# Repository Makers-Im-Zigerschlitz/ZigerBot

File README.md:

# ZigerBot

Arduino shield to teach STEM / basic robotics

Current state: _planning_ 

## Goal

Create an Arduino(R) shield to help teach STEM / basic robotics

## General idea

We love teaching about mechanics, electricity, electronics and robotics. ZigerBot allows us to have a robust platform to teach the very basic of all this. Participants build their own robotic platform, solder the ZigerBot shield and connect both. ZigerBot can then be programmed via Arduino IDE or ArduBlockly .

## Inspiration
https://github.com/FuzzyNoodle/Fuzzy-Naked-Mega

## Features for first iteration
- Arduino compatible with Atmega2560 and CP2102
- Power-Input: Drives ZigerBot and powers Arduino
- Drives two DC motors, connect with screw terminals (DRV8833PW)
- Prepared for 1-2 Ultrasonic Range Sensor (SR04)
- Has an RGB LED matrix (5x5 or bigger, WS2812B)
- Can play simple melodies or signal tones
- Has 4 tactile button inputs
- Has 1-2 potentiometers
- Has 4 Servo Outputs

## Dependencies
- FastLED Library
- Arduino Bootloader

## Pin Configuration

We try to minimalize conflicts with different in- and output components and their libraries. 

# ZigerBot

Arduino shield to teach STEM / basic robotics

Current state: _planning_ 

## Goal

Create an Arduino(R) shield to help teach STEM / basic robotics

## General idea

We love teaching about mechanics, electricity, electronics and robotics. ZigerBot allows us to have a robust platform to teach the very basic of all this. Participants build their own robotic platform, solder the ZigerBot shield and connect both. ZigerBot can then be programmed via Arduino IDE or ArduBlockly .

## Inspiration
https://github.com/FuzzyNoodle/Fuzzy-Naked-Mega

## Features for first iteration
- Arduino compatible with Atmega2560 and CP2102
- Power-Input: Drives ZigerBot and powers Arduino
- Drives two DC motors, connect with screw terminals
- Prepared for 1 Ultrasonic Range Sensor (SR04)
- Has an RGB LED matrix (5x5 or bigger, WS2812B)
- Can play simple melodies or signal tones
- Has 4 tactile button inputs
- Has 1-2 potentiometers
- Has 4 Servo Outputs

## Dependencies
- FastLED Library
- Arduino IDE, bootloader and generally Arduino libraries

## Pin Configuration

We try to minimalize conflicts with different in- and output components and their libraries. 

~ PWM

- Timer 0 is used by delay(), millis() and micros() - these functions are useful to beginners
- Timer 2 is used by the tone library
- Timer 5 is used by the servo/megaservo library for up to 12 servos

| Arduino IDE pin | ZigerBot | Special function |
| --- | --- | --- |
| D0 | not assigned | Tx0 |
| D1 | not assigned | Rx0 |
| D2~ | not assigned | Timer 3 |
| D3~ | not assigned | Timer 3 |
| D4~ | not assigned | Timer 0 |
| D5~ | **Motor A Input 1** | Timer 3 |
| D6~ | **Motor A Input 2** | Timer 4 |
| D7~ | **Motor B Input 1** | Timer 4 |
| D8~ | **Motor B Input 2** | Timer 4 |
| D9~ | not assigned | Timer 2 |
| D10~ | not assigned | Timer 2 |
| D11~ | not assigned | Timer 1 |
| D12~ | not assigned | Timer 1 |
| D13~ | not assigned | Timer 0, built-in LED|
| D14 | not assigned | Tx3 |
| D15 | not assigned | Rx3 |
| D16 | not assigned | Tx2 |
| D17 | not assigned | Rx2 |
| D18 | not assigned | Tx1 |
| D19 | not assigned | Rx1 |
| D20 | not assigned | SDA |
| D21 | not assigned | SCL |
| D22 | **Ultrasonic sensor SR04 trigger pin** | none |
| D23 | **Ultrasonic sensor SR04 echo pin** | none |
| D24 | **LED-Matrix data out** | none |
| D25 | **Piezo speaker** | none |
| D26 | **Tactile button 1** | none |
| D27 | **Tactile button 2** | none |
| D28 | **Tactile button 3** | none |
| D29 | **Tactile button 4** | none |
| D30 | **Servo 1** | none |
| D31 | **Servo 2** | none |
| D32 | **Servo 3** | none |
| D33 | **Servo 4** | none |
| D34 | not assigned | none |
| D35 | not assigned | none |
| D36 | not assigned | none |
| D37 | not assigned | none |
| D38 | not assigned | none |
| D39 | not assigned | none |
| D40 | not assigned | none |
| D41 | not assigned | none |
| D42 | not assigned | none |
| D43 | not assigned | none |
| D44~ | not assigned | Timer 5 |
| D45~ | not assigned | Timer 5 |
| D46~ | not assigned | Timer 5 |
| D47 | not assigned | none |
| D48 | not assigned | none |
| D49 | not assigned | none |
| D50 | not assigned | MISO |
| D51 | not assigned | MOSI |
| D52 | not assigned | SCK |
| D53 | not assigned | SS |
| --- | --- | --- |
| A0 | **Potentiometer 1** | none |
| A1 | **Potentiometer 2** | none |
| A2 | not assigned | none |
| A3 | not assigned | none |
| A4 | not assigned | none |
| A5 | not assigned | none |
| A6 | not assigned | none |
| A7 | not assigned | none |
| A8 | not assigned | none |
| A9 | not assigned | none |
| A10 | not assigned | none |
| A11 | not assigned | none |
| A12 | not assigned | none |
| A13 | not assigned | none |
| A14 | not assigned | none |
| A15 | not assigned | none |

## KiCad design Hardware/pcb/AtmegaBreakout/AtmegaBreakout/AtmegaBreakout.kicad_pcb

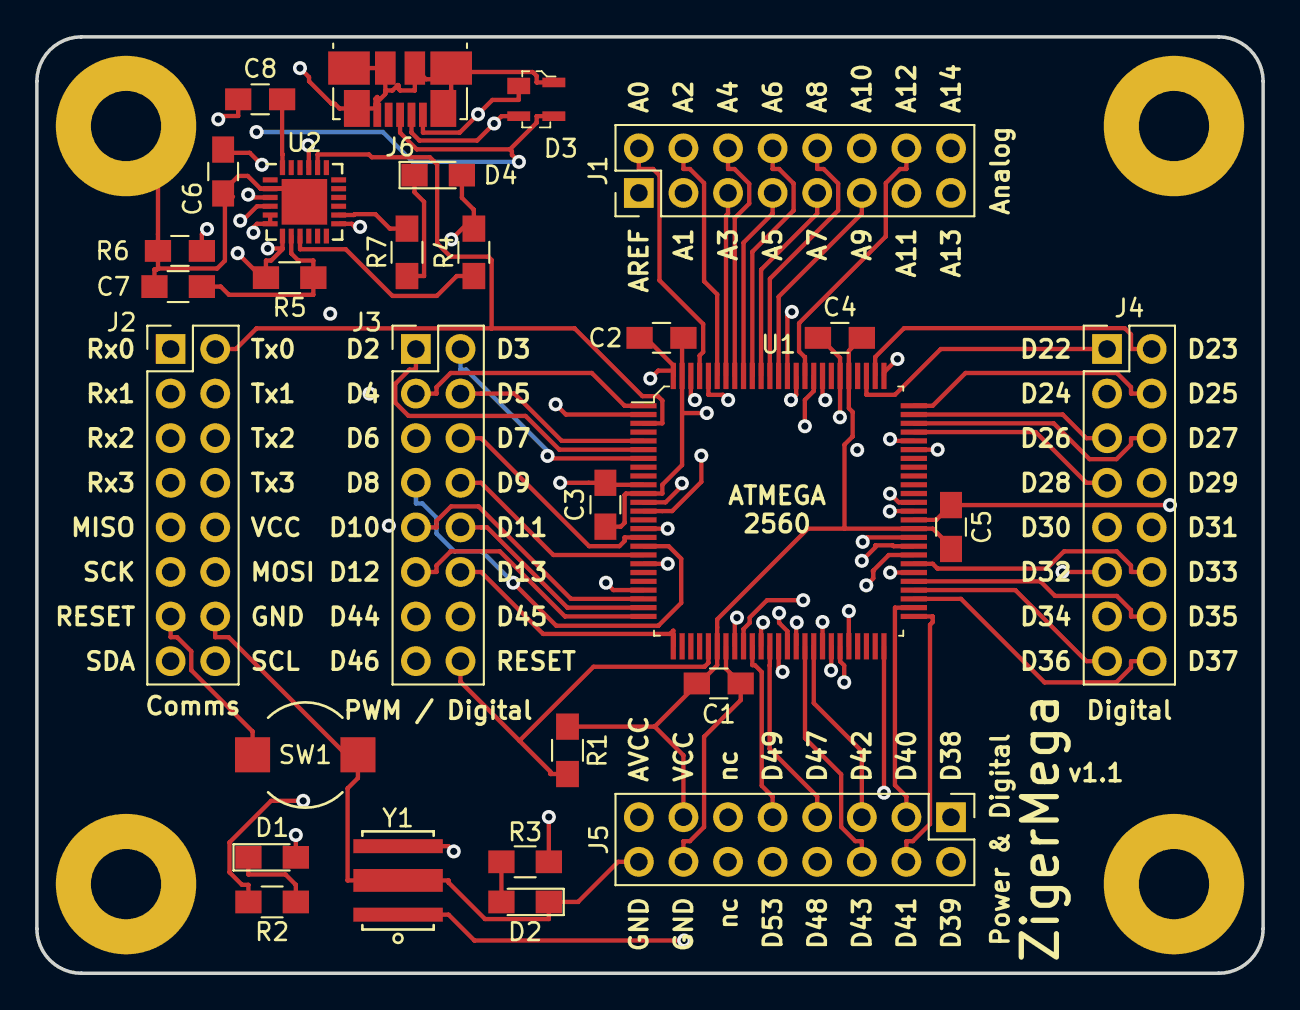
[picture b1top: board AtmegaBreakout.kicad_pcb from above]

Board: 4 copper layers, 69.9 x 53.3 mm, 33 parts (0 on the bottom side), 85 nets.

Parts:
C1, C2, C3, C4, C5, C6, C8: 0.1uF; C_0805_HandSoldering
C7: 4.7uF; C_0805_HandSoldering
D1: LED USB Rx; LED_0805_HandSoldering
D2: LED L; LED_0805_HandSoldering
D3: SP0503BAHTG; SOT-143-4
D4: LED USB Tx; LED_0805_HandSoldering
J1: ANALOG; Pin_Header_Straight_2x08_Pitch2.54mm
J2: POWER and COMMS; Pin_Header_Straight_2x08_Pitch2.54mm
J3: DIGITAL1; Pin_Header_Straight_2x08_Pitch2.54mm
J4: DIGITAL2; Pin_Header_Straight_2x08_Pitch2.54mm
J5: DIGITAL3; Pin_Header_Straight_2x08_Pitch2.54mm
J6: USB_B_Micro; USB_Micro-B_Molex_47346-0001
MH1, MH2, MH3, MH4: MountingHole_Pad; MountingHole_4mm_Pad
R1: 47k; R_0805_HandSoldering
R2, R3, R4, R7: 1k; R_0805_HandSoldering
R5: 22.1k; R_0805_HandSoldering
R6: 47.5k; R_0805_HandSoldering
SW1: EVP-ASAC1A
U1: ATMEGA2560-16AU; TQFP-100_14x14mm
U2: CP2102N-A01-GQFN24; QFN-24-1EP_4x4mm_Pitch0.5mm
Y1: 16MHz Ceramic Resonator; AWSCR-MT

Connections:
/A0: J1.2, U1.97
/A1: J1.3, U1.96
/A2: J1.4, U1.95
/A3: J1.5, U1.94
/A4: J1.6, U1.93
/A5: J1.7, U1.92
/A6: J1.8, U1.91
/A7: J1.9, U1.90
/A8: J1.10, U1.89
/A9: J1.11, U1.88
/A10: J1.12, U1.87
/A11: J1.13, U1.86
/A12: J1.14, U1.85
/A13: J1.15, U1.84
/A14: J1.16, U1.83
/AREF: J1.1, U1.98
/AVCC: C2.2, J5.15, U1.100
/D2: J3.1, U1.6
/D3: J3.2, U1.7
/D4: J3.3, U1.1
/D5: J3.4, U1.5
/D6: J3.5, U1.15
/D7: J3.6, U1.16
/D8: J3.7, U1.17
/D9: J3.8, U1.18
/D10: J3.9, U1.23
/D11: J3.10, U1.24
/D12: J3.11, U1.25
/D13: J3.12, R3.2, U1.26
/D22: J4.1, U1.78
/D23: J4.2, U1.77
/D24: J4.3, U1.76
/D25: J4.4, U1.75
/D26: J4.5, U1.74
/D27: J4.6, U1.73
/D28: J4.7, U1.72
/D29: J4.8, U1.71
/D30: J4.9, U1.60
/D31: J4.10, U1.59
/D32: J4.11, U1.58
/D33: J4.12, U1.57
/D34: J4.13, U1.56
/D35: J4.14, U1.55
/D36: J4.15, U1.54
/D37: J4.16, U1.53
/D38: J5.1, U1.50
/D39: J5.2, U1.70
/D40: J5.3, U1.52
/D41: J5.4, U1.51
/D42: J5.5, U1.42
/D43: J5.6, U1.41
/D44: J3.13, U1.40
/D45: J3.14, U1.39
/D46: J3.15, U1.38
/D47: J5.7, U1.37
/D48: J5.8, U1.36
/D49: J5.9, U1.35
/D53-SS: J5.10, U1.19
/DTR: C8.2, U2.24
/MISO-D50: J2.9, U1.22
/RESET: C8.1, J2.13, J3.16, R1.2, SW1.1, U1.30
/Rx0-D0: J2.1, U1.2, U2.21
/Rx1-D19: J2.3, U1.45
/Rx2-D17: J2.5, U1.12
/Rx3-D15: J2.7, U1.63
/SCL-D21: J2.16, U1.43
/SDA-D20: J2.15, U1.44
/Tx0-D1: J2.2, U1.3, U2.20
/Tx1-D18: J2.4, U1.46
/Tx2-D16: J2.6, U1.13
/Tx3-D14: J2.8, U1.64
/VIO: C6.2, C7.1, D1.2, D4.2, R4.2, U2.5, U2.6
/XTAL1: U1.34, Y1.3
/XTAL2: U1.33, Y1.1
GND: C1.1, C2.1, C3.1, C4.1, C5.1, C6.1, C7.2, D2.1, D3.1, J2.14, J5.14, J5.16, J6.5, J6.6, MH1.1, MH2.1, MH3.1, MH4.1, R6.1, SW1.2, U1.11, U1.32, U1.62, U1.81, U1.99, U2.2, U2.25, Y1.2
unnamed: D1.1, R2.1
unnamed: D2.2, R3.1
unnamed: D3.3, J6.2, U2.4
unnamed: D3.4, J6.3, U2.3
unnamed: D4.1, R7.1
unnamed: R2.2, U2.13
unnamed: R4.1, U2.9
unnamed: R5.1, R6.2, U2.8
unnamed: R7.2, U2.14
VCC: C1.2, C3.2, C4.2, C5.2, D3.2, J2.10, J5.13, J6.1, R1.1, R5.2, U1.10, U1.31, U1.61, U1.80, U2.7

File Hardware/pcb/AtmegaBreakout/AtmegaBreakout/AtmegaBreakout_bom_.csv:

Component,Description,Part,References,Value,Footprint,Quantity Per PCB,Datasheet,MPN,Digi-Key_PN,Category,Status,Family,DK_Datasheet_Link,DK_Detail_Page,Manufacturer
1,Unpolarized capacitor,C_Small,C1 C2 C3 C4 C5 C6 C8,0.1uF,C_0805_HandSoldering,7,~,CC0805ZRY5V9BB104,311-1361-1-ND,,,,,,
2,Unpolarized capacitor,C_Small,C7,4.7uF,C_0805_HandSoldering,1,~,CC0805ZRY5V6BB475,311-1371-1-ND,,,,,,
3,"LED, small symbol",LED_Small,D2,LED L,LED_0805_HandSoldering,1,~,LTST-C170GKT,160-1179-1-ND,,,,,,
4,"LED, small symbol",LED_Small,D1,LED USB Rx,LED_0805_HandSoldering,1,~,LTST-C171KSKT,160-1428-1-ND,,,,,,
5,"LED, small symbol",LED_Small,D4,LED USB Tx,LED_0805_HandSoldering,1,~,LTST-C171KSKT,160-1428-1-ND,,,,,,
6,TVS DIODE 5.5V 8.5V SOT143-4,SP0503BAHTG,D3,SP0503BAHTG,SOT-143-4,1,http://www.littelfuse.com/~/media/files/littelfuse/technical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,SP0503BAHTG,F2715CT-ND,Circuit Protection,Active,TVS - Diodes,http://www.littelfuse.com/~/media/files/littelfuse/technical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,/product-detail/en/littelfuse-inc/SP0503BAHTG/F2715CT-ND/1154322,Littelfuse Inc.
7,"Generic connector, double row, 02x08, odd/even pin numbering scheme (row 1 odd numbers, row 2 even numbers), script generated (kicad-library-utils/schlib/autogen/connector/)",Conn_02x08_Odd_Even,J1,ANALOG,Pin_Header_Straight_2x08_Pitch2.54mm,1,~,68602-116HLF,609-3364-ND,,,,,,
8,"Generic connector, double row, 02x08, odd/even pin numbering scheme (row 1 odd numbers, row 2 even numbers), script generated (kicad-library-utils/schlib/autogen/connector/)",Conn_02x08_Odd_Even,J3,DIGITAL1,Pin_Header_Straight_2x08_Pitch2.54mm,1,~,68602-116HLF,609-3364-ND,,,,,,
9,"Generic connector, double row, 02x08, odd/even pin numbering scheme (row 1 odd numbers, row 2 even numbers), script generated (kicad-library-utils/schlib/autogen/connector/)",Conn_02x08_Odd_Even,J4,DIGITAL2,Pin_Header_Straight_2x08_Pitch2.54mm,1,~,68602-116HLF,609-3364-ND,,,,,,
10,"Generic connector, double row, 02x08, odd/even pin numbering scheme (row 1 odd numbers, row 2 even numbers), script generated (kicad-library-utils/schlib/autogen/connector/)",Conn_02x08_Odd_Even,J5,DIGITAL3,Pin_Header_Straight_2x08_Pitch2.54mm,1,~,68602-116HLF,609-3364-ND,,,,,,
11,"Generic connector, double row, 02x08, odd/even pin numbering scheme (row 1 odd numbers, row 2 even numbers), script generated (kicad-library-utils/schlib/autogen/connector/)",Conn_02x08_Odd_Even,J2,POWER and COMMS,Pin_Header_Straight_2x08_Pitch2.54mm,1,~,68602-116HLF,609-3364-ND,,,,,,
12,USB Micro Type B connector,USB_B_Micro,J6,USB_B_Micro,USB_Micro-B_Molex_47346-0001,1,~,47346-0001,WM17141CT-ND,,,,,,
13,Resistor,R,R2 R3 R4 R7,1k,R_0805_HandSoldering,4,~,RC0805FR-071KL,311-1.00KCRCT-ND,,,,,,
14,Resistor,R,R5,22.1k,R_0805_HandSoldering,1,~,RC0805FR-0722K1L,311-22.1KCRCT-ND,,,,,,
15,Resistor,R,R6,47.5k,R_0805_HandSoldering,1,~,RC0805FR-0747K5L,311-47.5KCRCT-ND,,,,,,
16,Resistor,R,R1,47k,R_0805_HandSoldering,1,~,RC0805FR-0747KL,311-47.0KCRCT-ND,,,,,,
17,"Push button switch, generic, two pins",SW_Push,SW1,EVP-ASAC1A,EVP-ASAC1A,1,,EVP-ASAC1A,P16854CT-ND,,,,,,
18,IC MCU 8BIT 256KB FLASH 100TQFP,ATMEGA2560-16AU,U1,ATMEGA2560-16AU,TQFP-100_14x14mm,1,http://ww1.microchip.com/downloads/en/DeviceDoc/Atmel-2549-8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,ATMEGA2560-16AU,ATMEGA2560-16AU-ND,Integrated Circuits (ICs),Active,Embedded - Microcontrollers,http://ww1.microchip.com/downloads/en/DeviceDoc/Atmel-2549-8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,/product-detail/en/microchip-technology/ATMEGA2560-16AU/ATMEGA2560-16AU-ND/735455,Microchip Technology
19,USB to UART master bridge,CP2102N-A01-GQFN24,U2,CP2102N-A01-GQFN24,QFN-24-1EP_4x4mm_Pitch0.5mm,1,http://www.silabs.com/support%20documents/technicaldocs/cp21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,CP2102N-A01-GQFN24,336-4737-1-ND,,,,,,
20,Three pin ceramic resonator,Resonator,Y1,16MHz Ceramic Resonator,AWSCR-MT,1,~,AWSCR-16.00MTD-T,535-9362-1-ND,,,,,,





Component Groups:,20
Component Count:,29
Fitted Components:,29
Number of PCBs:,1
Total components:,29
Schematic Version:,
Schematic Date:,
BoM Date:,27/01/2019 21:54:11
Schematic Source:,C:\Users\Mike\Documents\GitHub\ZigerBot\Hardware\pcb\AtmegaBreakout\AtmegaBreakout\AtmegaBreakout.sch
KiCad Version:,Eeschema (5.0.0)

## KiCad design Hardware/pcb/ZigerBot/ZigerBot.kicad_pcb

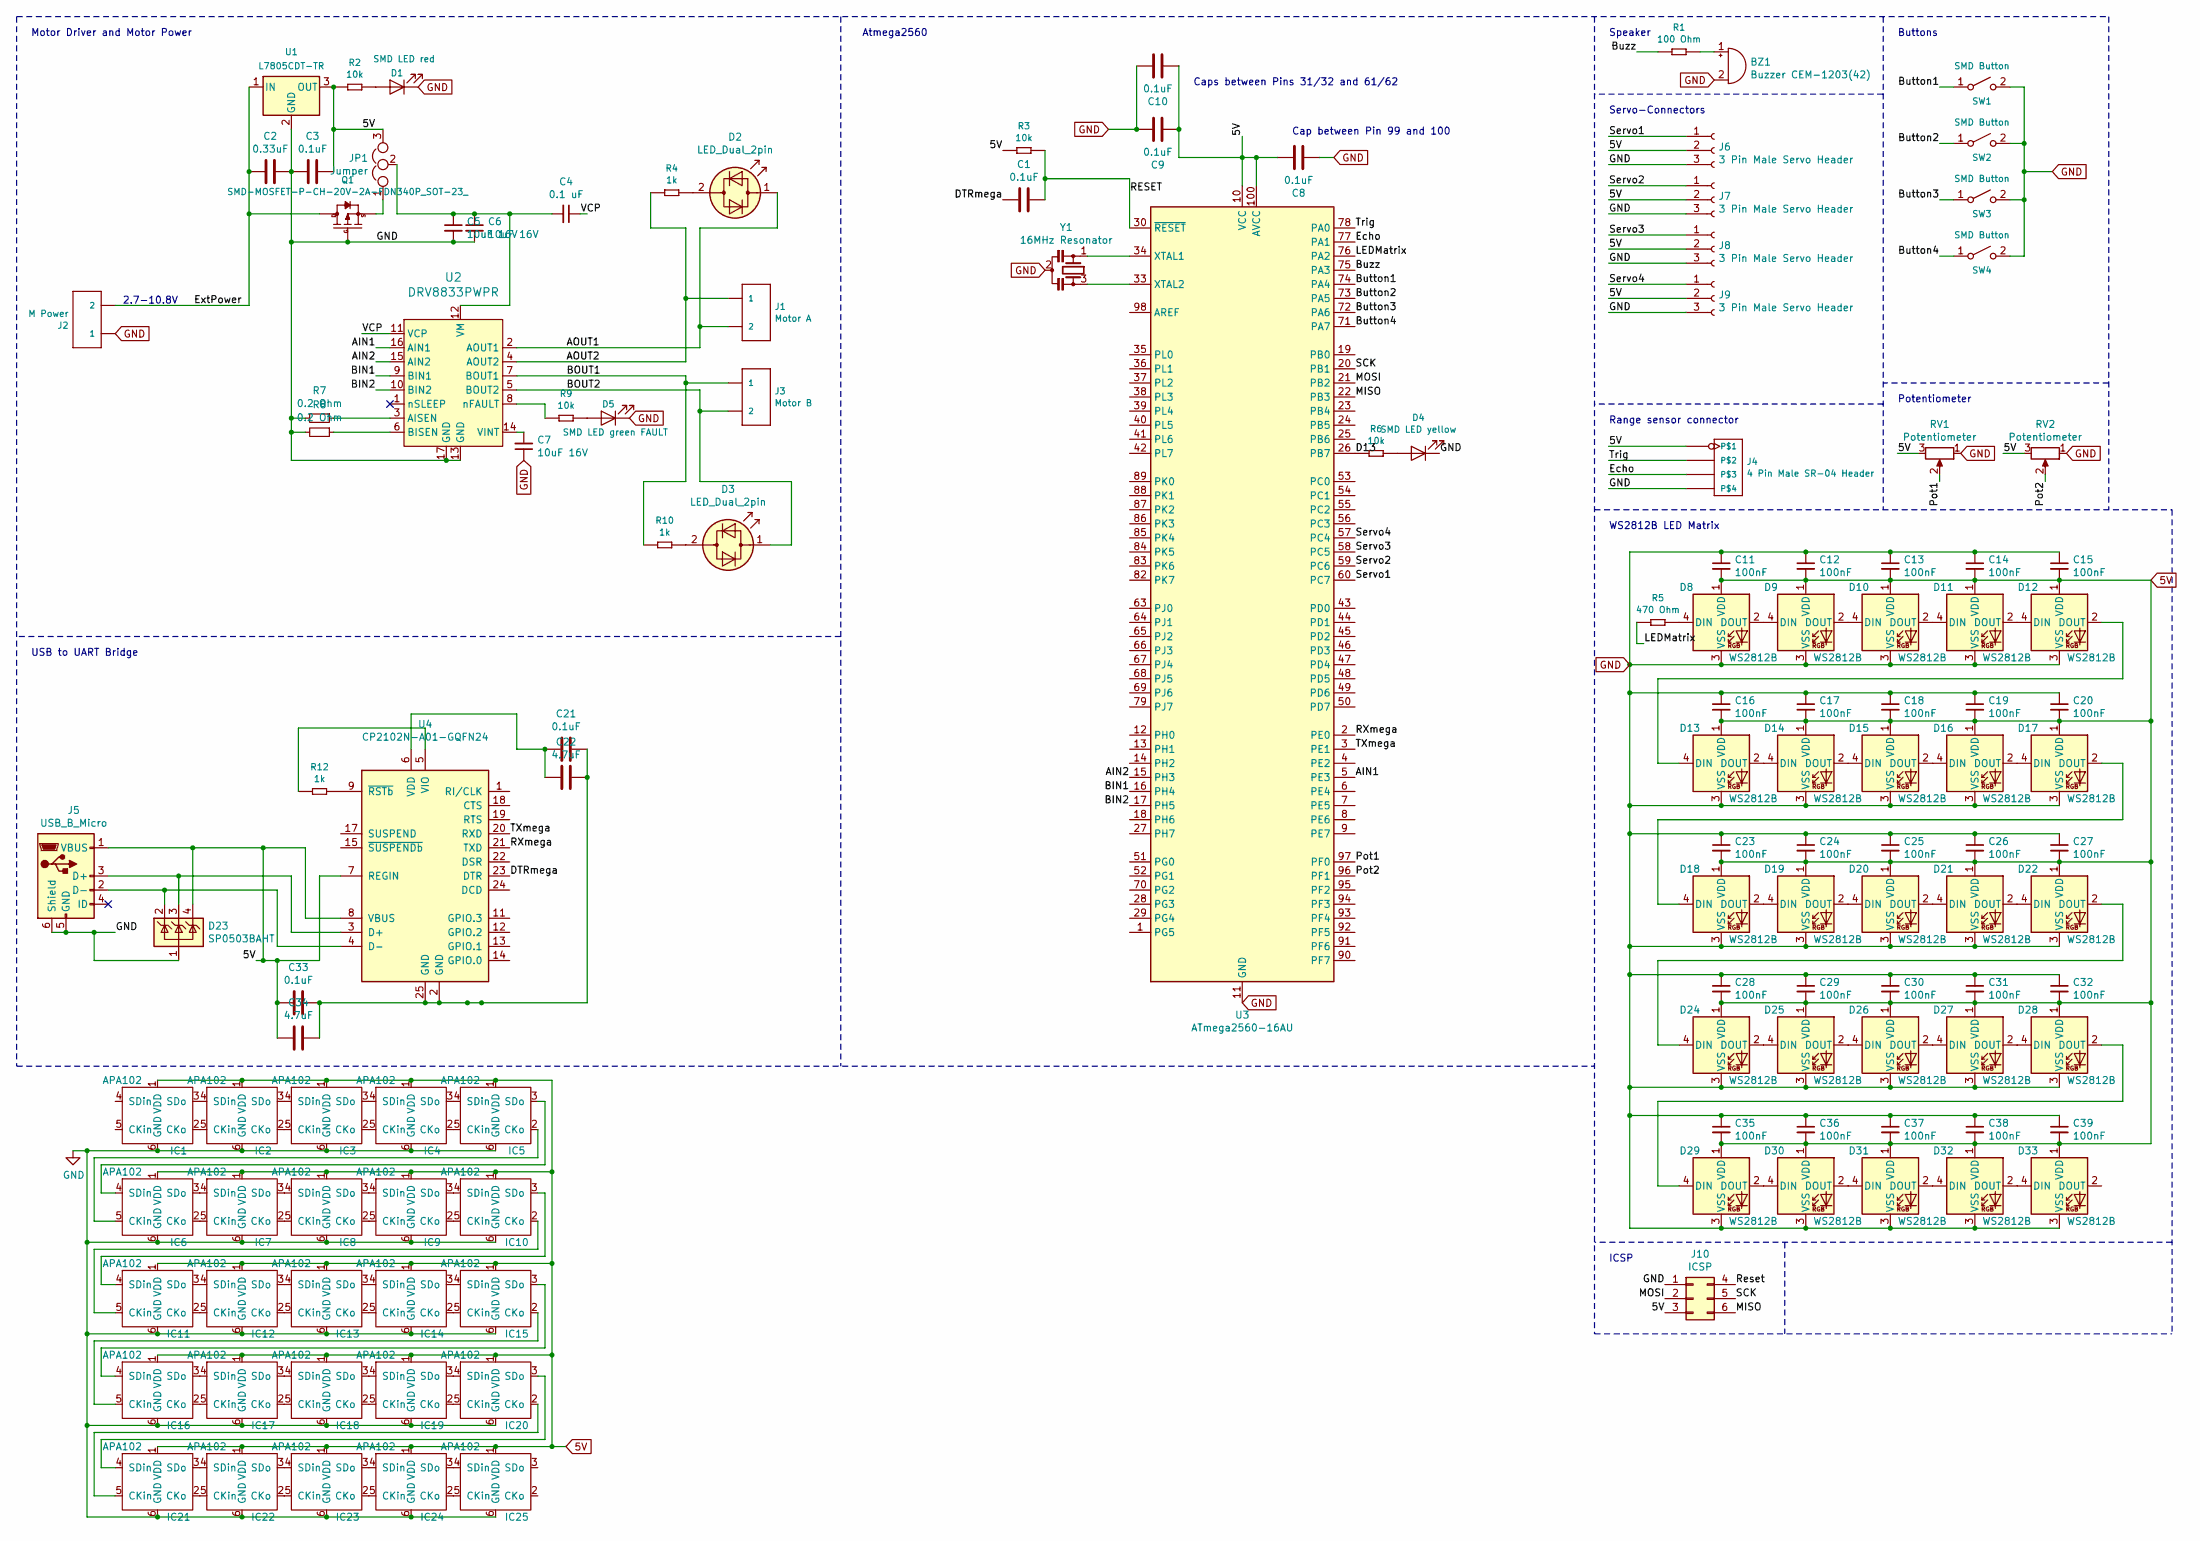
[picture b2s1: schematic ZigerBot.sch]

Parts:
BZ1: Buzzer CEM-1203(42); BUZZER_CEM-1203(24)_12mm_6.5mm_0.6mm; Digi-Key_PN 102-1153-ND
C1, C3, C8, C9, C10, C21, C33: 0.1uF; C_0805; Digi-Key_PN 311-1141-1-ND
C2: 0.33uF; C_0805; Digi-Key_PN 311-3385-1-ND
C4: 0.1 uF; C_0805; Digi-Key_PN 311-1141-1-ND
C5, C6, C7: 10uF 16V; C_0805; Digi-Key_PN 490-3886-1-ND
C11, C12, C13, C14, C15, C16, C17, C18, C19, C20, C23, C24, C25, C26, C27, C28, C29, C30, C31, C32, C35, C36, C37, C38, C39: 100nF; C_0805; Digi-Key_PN 311-1141-1-ND
C22, C34: 4.7uF; C_0805; Digi-Key_PN 311-1863-1-ND
D1: SMD LED red; LED_0603; Digi-Key_PN 160-1436-1-ND
D2, D3: LED_Dual_2pin; LED_D5.0mm; MPN LTL-293SJW; Digi-Key_PN 160-1038-ND
D4: SMD LED yellow; LED_0603; Digi-Key_PN 160-1437-1-ND
D5: SMD LED green FAULT; LED_0603; Digi-Key_PN 160-1435-1-ND
D8, D9, D10, D11, D12, D13, D14, D15, D16, D17, D18, D19, D20, D21, D22, D24, D25, D26, D27, D28, D29, D30, D31, D32, D33: WS2812B; LED_WS2812B-PLCC4; Digi-Key_PN 1528-1104-ND
D23: SP0503BAHT; SOT-143_Handsoldering; Digi-Key_PN F2715CT-ND
IC1, IC2, IC3, IC4, IC5, IC6, IC7, IC8, IC9, IC10, IC11, IC12, IC13, IC14, IC15, IC16, IC17, IC18, IC19, IC20, IC21, IC22, IC23, IC24, IC25: APA102; APA102-2020
J1: Motor A; H2-5.0-10.5X8.0MM; Digi-Key_PN ED2609-ND
J2: M Power; H2-5.0-10.5X8.0MM; Digi-Key_PN ED2609-ND
J3: Motor B; H2-5.0-10.5X8.0MM; Digi-Key_PN ED2609-ND
J4: 4 Pin Male SR-04 Header; H4-2.54; MPN P125-1104A0BS116A1; Digi-Key_PN 732-5317-ND
J5: USB_B_Micro; USB_Micro-B_Molex-105017-0001; Digi-Key_PN 609-4616-1-ND
J6, J7, J8, J9: 3 Pin Male Servo Header; Pin_Header_Straight_1x03_Pitch2.54mm; Digi-Key_PN 732-5316-ND
J10: ICSP; Digi-Key_PN 609-3218-ND
JP1: Jumper; Pin_Header_Straight_1x03_Pitch2.54mm; Digi-Key_PN 732-5316-ND
Q1: SMD-MOSFET-P-CH-20V-2A-FDN340P_SOT-23_; SOT-23; MPN FDN340P; Digi-Key_PN FDN340PCT-ND
R1: 100 Ohm; R_0805; Digi-Key_PN 311-100CRCT-ND
R2, R3, R6, R9: 10k; R_0805; Digi-Key_PN 311-10.0KCRCT-ND
R4, R10, R12: 1k; R_0805; Digi-Key_PN 311-1.00KCRCT-ND
R5: 470 Ohm; R_0805; Digi-Key_PN 311-470CRCT-ND
R7, R8: 0.2 Ohm; R_0805; Digi-Key_PN 311-.20SCT-ND
RV1, RV2: Potentiometer; Potentiometer_Trimmer-EVM3E; Digi-Key_PN 1528-1997-ND
SW1, SW2, SW3, SW4: SMD Button; SW_SPST_SKQG; MPN PTS645SK50SMTR92 LFS; Digi-Key_PN CKN9087CT-ND
U1: L7805CDT-TR; TO-252-2; MPN L7805CDT-TR; Digi-Key_PN 497-7255-1-ND
U2: DRV8833PWPR; TSSOP-16-1EP_W4.40mm; MPN DRV8833PWPR; Digi-Key_PN 296-29434-1-ND
U3: ATmega2560-16AU; TQFP-100_14x14mm_Pitch0.5mm; Digi-Key_PN ATMEGA2560-16AU-ND
U4: CP2102N-A01-GQFN24; QFN-24-1EP_4x4mm_Pitch0.5mm; Digi-Key_PN 336-4737-1-ND
Y1: 16MHz Resonator; Resonator_SMD_muRata_CSTNE16M0V530000_3pin_3.2x1.3x0.9mm; Digi-Key_PN CSTNE16M0V53C000R0

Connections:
5V: C3.1, C8.1, C9.2, C10.2, C11.2, C12.2, C13.2, C14.2, C15.2, C16.2, C17.2, C18.2, C19.2, C20.2, C23.2, C24.2, C25.2, C26.2, C27.2, C28.2, C29.2, C30.2, C31.2, C32.2, C33.2, C34.2, C35.2, C36.2, C37.2, C38.2, C39.2, D8.1 (VDD), D9.1 (VDD), D10.1 (VDD), D11.1 (VDD), D12.1 (VDD), D13.1 (VDD), D14.1 (VDD), D15.1 (VDD), D16.1 (VDD), D17.1 (VDD), D18.1 (VDD), D19.1 (VDD), D20.1 (VDD), D21.1 (VDD), D22.1 (VDD), D23.4 (K), D24.1 (VDD), D25.1 (VDD), D26.1 (VDD), D27.1 (VDD), D28.1 (VDD), D29.1 (VDD), D30.1 (VDD), D31.1 (VDD), D32.1 (VDD), D33.1 (VDD), IC1.1 (VDD), IC2.1 (VDD), IC3.1 (VDD), IC4.1 (VDD), IC5.1 (VDD), IC6.1 (VDD), IC7.1 (VDD), IC8.1 (VDD), IC9.1 (VDD), IC10.1 (VDD), IC11.1 (VDD), IC12.1 (VDD), IC13.1 (VDD), IC14.1 (VDD), IC15.1 (VDD), IC16.1 (VDD), IC17.1 (VDD), IC18.1 (VDD), IC19.1 (VDD), IC20.1 (VDD), IC21.1 (VDD), IC22.1 (VDD), IC23.1 (VDD), IC24.1 (VDD), IC25.1 (VDD), J4.1, J5.1 (VBUS), J6.2, J7.2, J8.2, J9.2, J10.3, JP1.3, R2.1, R3.1, RV1.3, RV2.3, U1.3 (OUT), U3.10 (VCC), U3.31 (VCC), U3.61 (VCC), U3.80 (VCC), U3.100 (AVCC), U4.7 (REGIN), U4.8 (VBUS)
/AIN1: U2.16 (AIN1), U3.5 (PE3)
/AIN2: U2.15 (AIN2), U3.15 (PH3)
/AOUT1: D2.1 (KA), J1.2, U2.2 (AOUT1)
/AOUT2: J1.1, R4.1, U2.4 (AOUT2)
/BIN1: U2.9 (BIN1), U3.16 (PH4)
/BIN2: U2.10 (BIN2), U3.17 (PH5)
/BOUT1: J3.1, R10.1, U2.7 (BOUT1)
/BOUT2: D3.1 (KA), J3.2, U2.5 (BOUT2)
/Button1: SW1.1 (A), U3.74 (PA4)
/Button2: SW2.1 (A), U3.73 (PA5)
/Button3: SW3.1 (A), U3.72 (PA6)
/Button4: SW4.1 (A), U3.71 (PA7)
/Buzz: R1.1, U3.75 (PA3)
/D13: R6.1, U3.26 (PB7)
/DTRmega: C1.2, U4.23 (DTR)
/Echo: J4.3, U3.77 (PA1)
/ExtPower: C2.2, J2.2, Q1.3 (D), U1.1 (IN)
/LEDMatrix: R5.1, U3.76 (PA2)
/MISO: J10.6, U3.22 (PB3)
/MOSI: J10.2, U3.21 (PB2)
/Pot1: RV1.2, U3.97 (PF0)
/Pot2: RV2.2, U3.96 (PF1)
/RESET: C1.1, R3.2, U3.30 (~RESET)
/RXmega: U3.2 (PE0), U4.21 (TXD)
/Reset: J10.4
/SCK: J10.5, U3.20 (PB1)
/Servo1: J6.1, U3.60 (PC7)
/Servo2: J7.1, U3.59 (PC6)
/Servo3: J8.1, U3.58 (PC5)
/Servo4: J9.1, U3.57 (PC4)
/TXmega: U3.3 (PE1), U4.20 (RXD)
/Trig: J4.2, U3.78 (PA0)
/VCP: C4.1, U2.11 (VCP)
GND: BZ1.2 (+), C2.1, C3.2, C5.2, C6.2, C7.1, C8.2, C9.1, C10.1, C11.1, C12.1, C13.1, C14.1, C15.1, C16.1, C17.1, C18.1, C19.1, C20.1, C23.1, C24.1, C25.1, C26.1, C27.1, C28.1, C29.1, C30.1, C31.1, C32.1, C35.1, C36.1, C37.1, C38.1, C39.1, D1.1 (K), D4.1 (K), D5.1 (K), D8.3 (VSS), D9.3 (VSS), D10.3 (VSS), D11.3 (VSS), D12.3 (VSS), D13.3 (VSS), D14.3 (VSS), D15.3 (VSS), D16.3 (VSS), D17.3 (VSS), D18.3 (VSS), D19.3 (VSS), D20.3 (VSS), D21.3 (VSS), D22.3 (VSS), D23.1 (A), D24.3 (VSS), D25.3 (VSS), D26.3 (VSS), D27.3 (VSS), D28.3 (VSS), D29.3 (VSS), D30.3 (VSS), D31.3 (VSS), D32.3 (VSS), D33.3 (VSS), IC1.6 (GND), IC2.6 (GND), IC3.6 (GND), IC4.6 (GND), IC5.6 (GND), IC6.6 (GND), IC7.6 (GND), IC8.6 (GND), IC9.6 (GND), IC10.6 (GND), IC11.6 (GND), IC12.6 (GND), IC13.6 (GND), IC14.6 (GND), IC15.6 (GND), IC16.6 (GND), IC17.6 (GND), IC18.6 (GND), IC19.6 (GND), IC20.6 (GND), IC21.6 (GND), IC22.6 (GND), IC23.6 (GND), IC24.6 (GND), IC25.6 (GND), J2.1, J4.4, J5.5 (GND), J5.6 (Shield), J6.3, J7.3, J8.3, J9.3, J10.1, Q1.1 (G), R7.2, R8.2, RV1.1, RV2.1, SW1.2 (B), SW2.2 (B), SW3.2 (B), SW4.2 (B), U1.2 (GND), U2.13 (GND), U2.17 (GND), U3.11 (GND), U3.32 (GND), U3.62 (GND), U3.81 (GND), U3.99 (GND), Y1.2
unnamed: BZ1.1 (-), R1.2
unnamed: C4.2, C5.1, C6.1, JP1.2, U2.12 (VM)
unnamed: C7.2, U2.14 (VINT)
unnamed: C21.1, C22.1, C33.1, C34.1, U4.2 (GND), U4.10 (NC), U4.16 (NC), U4.25 (GND)
unnamed: C21.2, C22.2, U4.6 (VDD)
unnamed: D1.2 (A), R2.2
unnamed: D2.2 (AK), R4.2
unnamed: D3.2 (AK), R10.2
unnamed: D4.2 (A), R6.2
unnamed: D5.2 (A), R9.2
unnamed: D8.2 (DOUT), D9.4 (DIN)
unnamed: D8.4 (DIN), R5.2
unnamed: D10.2 (DOUT), D11.4 (DIN)
unnamed: D9.2 (DOUT), D10.4 (DIN)
unnamed: D11.2 (DOUT), D12.4 (DIN)
unnamed: D12.2 (DOUT), D13.4 (DIN)
unnamed: D13.2 (DOUT), D14.4 (DIN)
unnamed: D14.2 (DOUT), D15.4 (DIN)
unnamed: D15.2 (DOUT), D16.4 (DIN)
unnamed: D16.2 (DOUT), D17.4 (DIN)
unnamed: D17.2 (DOUT), D18.4 (DIN)
unnamed: D18.2 (DOUT), D19.4 (DIN)
unnamed: D19.2 (DOUT), D20.4 (DIN)
unnamed: D20.2 (DOUT), D21.4 (DIN)
unnamed: D21.2 (DOUT), D22.4 (DIN)
unnamed: D22.2 (DOUT), D24.4 (DIN)
unnamed: D23.2 (K), J5.2 (D-), U4.4 (D-)
unnamed: D23.3 (K), J5.3 (D+), U4.3 (D+)
unnamed: D24.2 (DOUT), D25.4 (DIN)
unnamed: D25.2 (DOUT), D26.4 (DIN)
unnamed: D26.2 (DOUT), D27.4 (DIN)
unnamed: D27.2 (DOUT), D28.4 (DIN)
unnamed: D28.2 (DOUT), D29.4 (DIN)
unnamed: D29.2 (DOUT), D30.4 (DIN)
unnamed: D30.2 (DOUT), D31.4 (DIN)
unnamed: D31.2 (DOUT), D32.4 (DIN)
unnamed: D32.2 (DOUT), D33.4 (DIN)
unnamed: IC1.2 (CKo), IC2.5 (CKin)
unnamed: IC1.3 (SDo), IC2.4 (SDin)
unnamed: IC2.2 (CKo), IC3.5 (CKin)
unnamed: IC2.3 (SDo), IC3.4 (SDin)
unnamed: IC3.2 (CKo), IC4.5 (CKin)
unnamed: IC3.3 (SDo), IC4.4 (SDin)
unnamed: IC4.2 (CKo), IC5.5 (CKin)
unnamed: IC4.3 (SDo), IC5.4 (SDin)
unnamed: IC5.2 (CKo), IC6.5 (CKin)
unnamed: IC5.3 (SDo), IC6.4 (SDin)
unnamed: IC6.2 (CKo), IC7.5 (CKin)
unnamed: IC6.3 (SDo), IC7.4 (SDin)
unnamed: IC7.2 (CKo), IC8.5 (CKin)
unnamed: IC7.3 (SDo), IC8.4 (SDin)
unnamed: IC8.2 (CKo), IC9.5 (CKin)
unnamed: IC8.3 (SDo), IC9.4 (SDin)
unnamed: IC10.2 (CKo), IC11.5 (CKin)
unnamed: IC10.3 (SDo), IC11.4 (SDin)
unnamed: IC9.3 (SDo), IC10.4 (SDin)
unnamed: IC9.2 (CKo), IC10.5 (CKin)
unnamed: IC11.2 (CKo), IC12.5 (CKin)
unnamed: IC11.3 (SDo), IC12.4 (SDin)
unnamed: IC12.2 (CKo), IC13.5 (CKin)
unnamed: IC12.3 (SDo), IC13.4 (SDin)
unnamed: IC13.2 (CKo), IC14.5 (CKin)
unnamed: IC13.3 (SDo), IC14.4 (SDin)
unnamed: IC14.2 (CKo), IC15.5 (CKin)
unnamed: IC14.3 (SDo), IC15.4 (SDin)
unnamed: IC15.2 (CKo), IC16.5 (CKin)
unnamed: IC15.3 (SDo), IC16.4 (SDin)
unnamed: IC16.2 (CKo), IC17.5 (CKin)
unnamed: IC16.3 (SDo), IC17.4 (SDin)
unnamed: IC17.2 (CKo), IC18.5 (CKin)
unnamed: IC17.3 (SDo), IC18.4 (SDin)
unnamed: IC18.2 (CKo), IC19.5 (CKin)
unnamed: IC18.3 (SDo), IC19.4 (SDin)
unnamed: IC19.2 (CKo), IC20.5 (CKin)
unnamed: IC19.3 (SDo), IC20.4 (SDin)
unnamed: IC20.2 (CKo), IC21.5 (CKin)
unnamed: IC20.3 (SDo), IC21.4 (SDin)
unnamed: IC21.2 (CKo), IC22.5 (CKin)
unnamed: IC21.3 (SDo), IC22.4 (SDin)
unnamed: IC22.2 (CKo), IC23.5 (CKin)
unnamed: IC22.3 (SDo), IC23.4 (SDin)
unnamed: IC23.2 (CKo), IC24.5 (CKin)
unnamed: IC23.3 (SDo), IC24.4 (SDin)
unnamed: IC24.2 (CKo), IC25.5 (CKin)
unnamed: IC24.3 (SDo), IC25.4 (SDin)
unnamed: JP1.1, Q1.2 (S)
unnamed: R7.1, U2.3 (AISEN)
unnamed: R8.1, U2.6 (BISEN)
unnamed: R9.1, U2.8 (nFAULT)
unnamed: R12.1, U4.5 (VIO)
unnamed: R12.2, U4.9 (~RSTb)
unnamed: U3.33 (XTAL2), Y1.3
unnamed: U3.34 (XTAL1), Y1.1

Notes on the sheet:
2.7-10.8V
Motor Driver and Motor Power
USB to UART Bridge
Atmega2560
Speaker
Servo-Connectors
Range sensor connector
WS2812B LED Matrix
Buttons
Potentiometer
Cap between Pin 99 and 100
Caps between Pins 31/32 and 61/62
ICSP

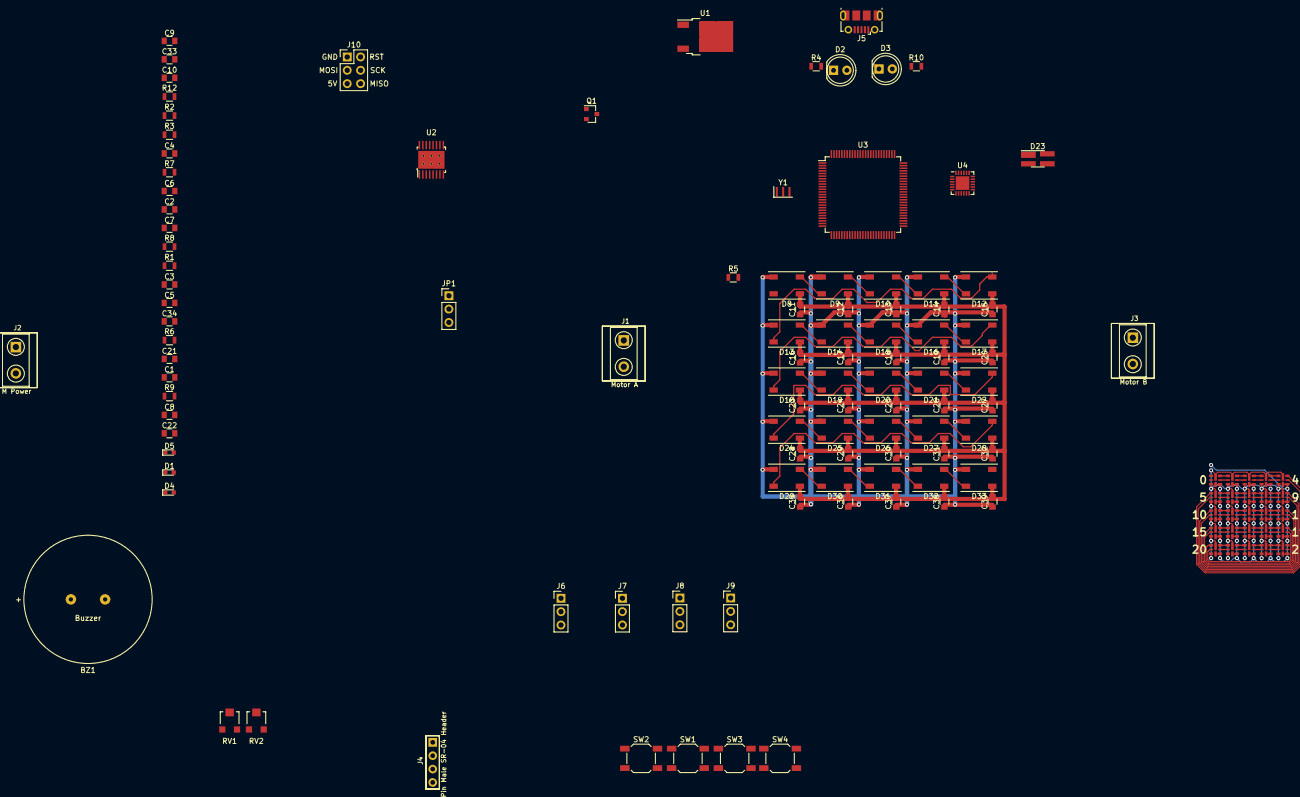
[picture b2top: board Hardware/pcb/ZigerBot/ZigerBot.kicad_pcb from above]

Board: 4 copper layers, 130 parts (0 on the bottom side), 127 nets.

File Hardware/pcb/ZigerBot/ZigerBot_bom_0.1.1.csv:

Component,Description,Part,References,Value,Footprint,Quantity Per PCB,Datasheet,Digi-Key_PN,MPN,SKU,Category,Status,Family,DK_Datasheet_Link,DK_Detail_Page,Manufacturer
1,"Buzzer, polar",Buzzer,BZ1,Buzzer CEM-1203(42),BUZZER_CEM-1203(24)_12mm_6.5mm_0.6mm,1,~,102-1153-ND,,,,,,,,
2,Unpolarized capacitor,C_Small,C4,0.1 uF,C_0805,1,~,311-1141-1-ND,,,,,,,,
3,Unpolarized capacitor,C,C1 C3 C8 C9 C10 C11 C12 C13 C14 C15 C16 C17 C18 C19 C20 C21 C23 C24 C25 C26 C27 C28 C29 C30 C31 C32 C33 C35 C36 C37 C38 C39,0.1uF,C_0805,32,~,311-1141-1-ND,,,,,,,,
4,Unpolarized capacitor,C,C2,0.33uF,C_0805,1,~,311-3385-1-ND,,,,,,,,
5,Unpolarized capacitor,C_Small,C5 C6 C7,10uF 16V,C_0805,3,~,490-3886-1-ND,,,,,,,,
6,Unpolarized capacitor,C,C22 C34,4.7uF,C_0805,2,~,311-1863-1-ND,,,,,,,,
7,"LED dual, 2pin version",LED_Dual_2pin,D2 D3,LED_Dual_2pin,LED_D5.0mm,2,~,160-1038-ND,LTL-293SJW,,,,,,,
8,LED generic,LED,D5,SMD LED green FAULT,LED_0603,1,,160-1435-1-ND,,,,,,,,
9,LED generic,LED,D1,SMD LED red,LED_0603,1,,160-1436-1-ND,,,,,,,,
10,LED generic,LED,D4,SMD LED yellow,LED_0603,1,,160-1437-1-ND,,,,,,,,
11,"TVS Diode Array, 5.5V Standoff, 3 Channels, SOT-143 package",SP0503BAHT,D23,SP0503BAHT,SOT-143_Handsoldering,1,http://www.littelfuse.com/~/media/files/littelfuse/technical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,F2715CT-ND,,,,,,,,
12,RGB LED with integrated controller,WS2812B,D8 D9 D10 D11 D12 D13 D14 D15 D16 D17 D18 D19 D20 D21 D22 D24 D25 D26 D27 D28 D29 D30 D31 D32 D33,WS2812B,LED_WS2812B-PLCC4,25,https://cdn-shop.adafruit.com/datasheets/WS2812B.pdf,1528-1104-ND,,,,,,,,
13,"Generic connector, single row, 01x03, script generated (kicad-library-utils/schlib/autogen/connector/)",Conn_01x03_Female,J6 J7 J8 J9,3 Pin Male Servo Header,Pin_Header_Straight_1x03_Pitch2.54mm,4,~,732-5316-ND,,,,,,,,
14,,DIP-BLACK-MALE-HEADER-VERT_4P-2.54_,J4,4 Pin Male SR-04 Header,H4-2.54,1,,732-5317-ND,P125-1104A0BS116A1,320020017,,,,,,
15,"Generic connector, double row, 02x03, top/bottom pin numbering scheme (row 1: 1...pins_per_row, row2: pins_per_row+1 ... num_pins), script generated (kicad-library-utils/schlib/autogen/connector/)",Conn_02x03_Top_Bottom,J10,ICSP,ICSP,1,~,609-3218-ND,,,,,,,,
16,,SCREW-TERMINAL-GREEN_2P-5.0_,J2,M Power,H2-5.0-10.5X8.0MM,1,,ED2609-ND,,320110031,,,,,,
17,,SCREW-TERMINAL-GREEN_2P-5.0_,J1,Motor A,H2-5.0-10.5X8.0MM,1,,ED2609-ND,,320110031,,,,,,
18,,SCREW-TERMINAL-GREEN_2P-5.0_,J3,Motor B,H2-5.0-10.5X8.0MM,1,,ED2609-ND,,320110031,,,,,,
19,USB Micro Type B connector,USB_B_Micro,J5,USB_B_Micro,USB_Micro-B_Molex-105017-0001,1,~,609-4616-1-ND,,,,,,,,
20,"Dual Jumper, normally closed",Jumper_NC_Dual,JP1,Jumper,Pin_Header_Straight_1x03_Pitch2.54mm,1,~,732-5316-ND,,,,,,,,
21,,SMD-MOSFET-P-CH-20V-2A-FDN340P_SOT-23_,Q1,SMD-MOSFET-P-CH-20V-2A-FDN340P_SOT-23_,SOT-23,1,,FDN340PCT-ND,FDN340P,305030026,,,,,,
22,"Resistor, small symbol",R_Small,R7 R8,0.2 Ohm,R_0805,2,~,311-.20SCT-ND,,,,,,,,
23,,SMD-RES-100R-5%-1_8W_0805_,R1,100 Ohm,R_0805,1,,311-100CRCT-ND,,301010319,,,,,,
24,,SMD-RES-1K-5%-1_8W_0805_,R2 R3 R6 R9,10k,R_0805,4,,311-10.0KCRCT-ND,,301010311,,,,,,
25,,SMD-RES-1K-5%-1_8W_0805_,R4 R10 R12,1k,R_0805,3,,311-1.00KCRCT-ND,,301010311,,,,,,
26,,SMD-RES-100R-5%-1_8W_0805_,R5,470 Ohm,R_0805,1,,311-470CRCT-ND,,301010319,,,,,,
27,Potentiometer,R_POT,RV1 RV2,Potentiometer,Potentiometer_Trimmer-EVM3E,2,~,1528-1997-ND,,,,,,,,
28,Single Pole Single Throw (SPST) switch,SW_SPST,SW1 SW2 SW3 SW4,SMD Button,SW_SPST_SKQG,4,,CKN9087CT-ND,PTS645SK50SMTR92 LFS,311020017,,,,,,
29,"16MHz, 256kB Flash, 8kB SRAM, 4kB EEPROM, JTAG, TQFP-100",ATmega2560-16AU,U3,ATmega2560-16AU,TQFP-100_14x14mm_Pitch0.5mm,1,http://ww1.microchip.com/downloads/en/DeviceDoc/Atmel-2549-8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,ATMEGA2560-16AU-ND,,,,,,,,
30,USB to UART master bridge,CP2102N-A01-GQFN24,U4,CP2102N-A01-GQFN24,QFN-24-1EP_4x4mm_Pitch0.5mm,1,http://www.silabs.com/support%20documents/technicaldocs/cp21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,336-4737-1-ND,,,,,,,,
31,IC MOTOR DRIVER PAR 16HTSSOP,DRV8833PWPR,U2,DRV8833PWPR,TSSOP-16-1EP_W4.40mm,1,http://www.ti.com/lit/ds/symlink/drv8833.pdf,296-29434-1-ND,DRV8833PWPR,,Integrated Circuits (ICs),Active,"PMIC - Full, Half-Bridge Drivers",http://www.ti.com/lit/ds/symlink/drv8833.pdf,/product-detail/en/texas-instruments/DRV8833PWPR/296-29434-1-ND/2743171,Texas Instruments
32,"Positive 1.5A 35V Linear Regulator, Fixed Output 5V, TO-220/TO-263/TO-252",L7805,U1,L7805CDT-TR,TO-252-2,1,http://www.st.com/content/ccc/resource/technical/document/da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,497-7255-1-ND,L7805CDT-TR,310030010,,,,,,
33,Three pin ceramic resonator,Resonator_Small,Y1,16MHz Resonator,Resonator_SMD_muRata_CSTNE16M0V530000_3pin_3.2x1.3x0.9mm,1,~,CSTNE16M0V53C000R0,,,,,,,,





Component Groups:,33
Component Count:,105
Fitted Components:,105
Number of PCBs:,1
Total components:,105
Schematic Version:,0.1.1
Schematic Date:,2018-10-10
BoM Date:,16/01/2019 02:12:57
Schematic Source:,C:\Users\Mike\Documents\GitHub\ZigerBot\Hardware\pcb\ZigerBot\ZigerBot.sch
KiCad Version:,Eeschema (5.0.0)

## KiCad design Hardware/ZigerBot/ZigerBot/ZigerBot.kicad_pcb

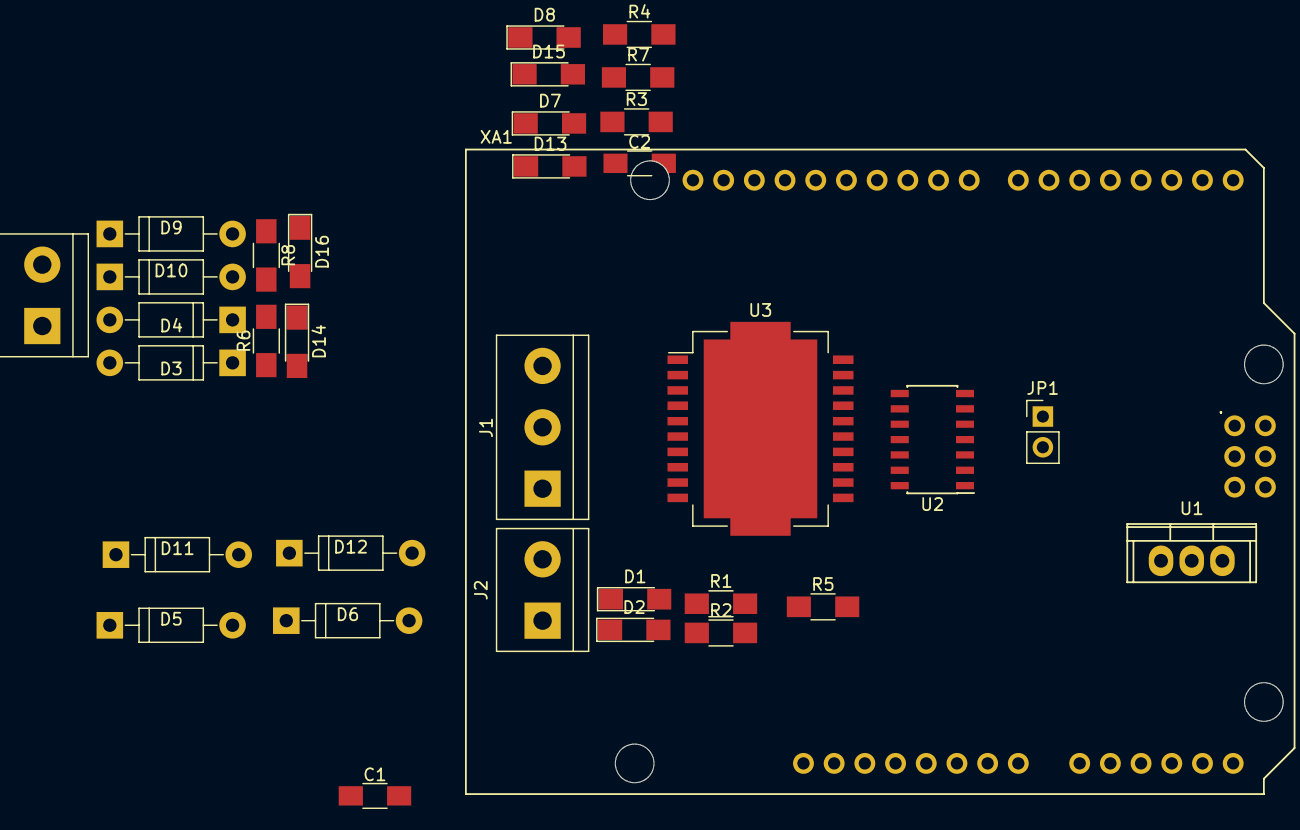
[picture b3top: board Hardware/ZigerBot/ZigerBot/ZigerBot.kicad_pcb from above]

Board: 2 copper layers, 34 parts (0 on the bottom side), 22 nets, no tracks yet.

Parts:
C1, C2: 0.1uF C1206S104M5RACTU; C_1206_HandSoldering
D1: LED Blue; LED_1206_HandSoldering
D2, D16: LED Yellow; LED_1206_HandSoldering
D3, D4, D5, D6, D9, D10, D11, D12: SR140; D_DO-41_SOD81_P10.16mm_Horizontal
D7, D8, D13, D15: LED Red; LED_1206_HandSoldering
D14: LED BLUE; LED_1206_HandSoldering
J1: Screw_Terminal_01x03; TerminalBlock_bornier-3_P5.08mm
J2, J3: Screw_Terminal_01x02; TerminalBlock_bornier-2_P5.08mm
JP1: Jumper; Pin_Header_Straight_1x02_Pitch2.54mm
R1, R2, R3, R4, R5, R6, R7, R8: 1k; R_1206_HandSoldering
U1: L7805; TO-220
U2: NXP 74HC04; SOIC-14_3.9x8.7mm_Pitch1.27mm
U3: L298P; HSOP-20-1EP_11.0x15.9mm_Pitch1.27mm_SlugDown
XA1: Arduino_Uno_Shield

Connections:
/D2: R3.2, U2.1, U3.7, XA1.D2
/D3: R4.2, U3.8, XA1.D3
/D4: R5.2, U2.3, U3.13, XA1.D4
/D11: R7.2, U3.14, XA1.D11
/VS: C2.1, J1.3, JP1.1, U3.6, XA1.VIN
GND: C1.2, C2.2, D7.1, D8.1, D9.2, D10.2, D11.2, D12.2, D13.1, D15.1, J1.1, U1.2, U2.7, U3.1, U3.10, U3.11, U3.20, XA1.GND1, XA1.GND2, XA1.GND3
unnamed: D1.1, D2.2, D5.2, D11.1, J2.2, U3.5
unnamed: D1.2, R1.1
unnamed: D2.1, R2.2
unnamed: D7.2, R3.1
unnamed: D8.2, R4.1
unnamed: D4.2, D10.1, J3.1, R6.2, R8.2, U3.16
unnamed: D6.2, D12.1, J2.1, R1.2, R2.1, U3.4
unnamed: D13.2, R5.1
unnamed: D3.2, D9.1, D14.1, D16.2, J3.2, U3.17
unnamed: D14.2, R6.1
unnamed: D15.2, R7.1
unnamed: D16.1, R8.1
unnamed: JP1.2, U1.1
unnamed: U2.2, U3.9
unnamed: U2.4, U3.15
VSS: C1.1, D3.1, D4.1, D5.1, D6.1, J1.2, U1.3, U2.14, U3.12, XA1.5V1

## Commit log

2018-10-06 Added Inspiration and Changed to On-Board Atmega and Serial-to-TTL chip
2018-10-06 Fixed Markdown
2018-10-08 Adds folder hierarchy and first kicad comit
2018-10-08 Erweiterte Ordnerstruktur
2018-10-08 adds submodule ardublockly
2018-10-08 and again changing the folder hierarchy
2018-10-08 Removed submodule ardublocky
2018-10-08 Add OPL
2018-10-08 changed submodule file
2018-10-11 PCB erweitert
2018-10-14 Added all peripheral components
2018-10-14 PCB changed
2018-10-28 Updated Package Info
2018-10-30 LED-Matrix routed
2018-10-31 changed pin mappings in README
2018-11-01 Added ICSP Header, Connected all peripherals to Atmega2560, updated README.md
2019-04-02 V1.1
2019-04-03 Groundplane, Missing GND and VCC connection
